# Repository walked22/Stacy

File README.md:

# Stacy

Control PCB for Modified 1995 Geo Tracker 

STACY is a is a custom built printed circuit board that remotely starts, warms up, locks, unlocks and 
tracks a 1995 Geo Tracker. The board was designed with expandability in mind allowing for future upgrades.

Features
- ARM Cortex M0+ microcontroller
- Easy locking connectors to withstand vibrations from offroad driving
- Extra connectors with both analog and digital I/O
- Can recieve commands from RFID and BLE
- Battery monitoring 
- Status RGB LED

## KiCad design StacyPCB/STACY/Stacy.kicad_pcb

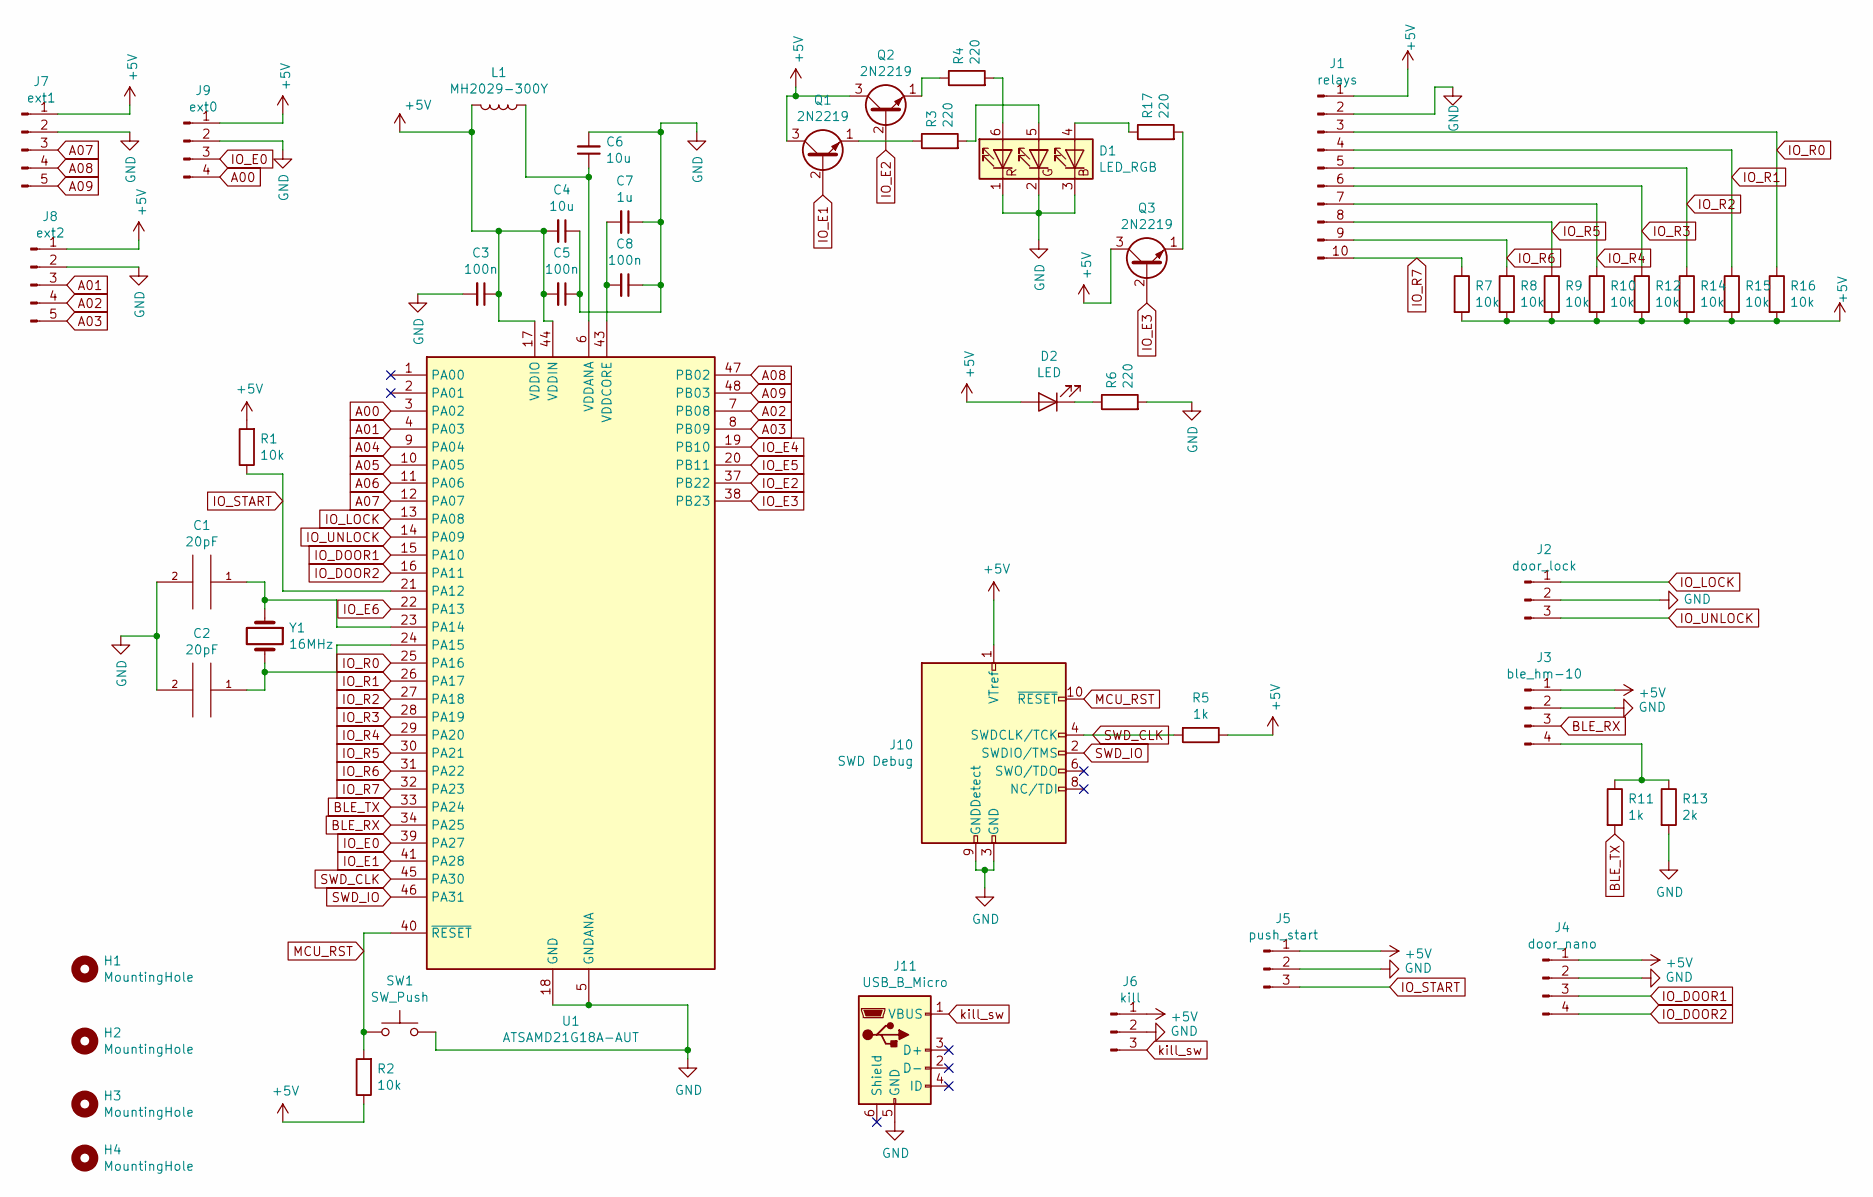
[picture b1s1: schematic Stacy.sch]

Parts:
C1, C2: 20pF; C_0402_1005Metric
C3, C5, C8: 100n; C_0402_1005Metric
C4, C6: 10u; C_0402_1005Metric
C7: 1u; C_0402_1005Metric
D1: LED_RGB; LED_RGB_PLCC-6
D2: LED; LED_0603_1608Metric
H1, H2, H3, H4: MountingHole; MountingHole_2.5mm
J1: relays; JST_EH_B10B-EH-A_1x10_P2.50mm_Vertical
J2: door_lock; JST_EH_B3B-EH-A_1x03_P2.50mm_Vertical
J3: ble_hm-10; JST_EH_B4B-EH-A_1x04_P2.50mm_Vertical
J4: door_nano; JST_EH_B4B-EH-A_1x04_P2.50mm_Vertical
J5: push_start; JST_EH_B3B-EH-A_1x03_P2.50mm_Vertical
J6: kill; JST_EH_B3B-EH-A_1x03_P2.50mm_Vertical
J7: ext1; JST_EH_B5B-EH-A_1x05_P2.50mm_Vertical
J8: ext2; JST_EH_B5B-EH-A_1x05_P2.50mm_Vertical
J9: ext0; JST_EH_B4B-EH-A_1x04_P2.50mm_Vertical
J10: SWD Debug; PinHeader_2x05_P1.27mm_Vertical
J11: USB_B_Micro; USB_Micro-B_Molex_47346-0001
L1: MH2029-300Y; L_0805_2012Metric
Q1, Q2, Q3: 2N2219; TSOT-23
R1, R2, R7, R8, R9, R10, R12, R14, R15, R16: 10k; R_0402_1005Metric
R3, R4, R6, R17: 220; R_0402_1005Metric
R5, R11: 1k; R_0402_1005Metric
R13: 2k; R_0402_1005Metric
SW1: SW_Push; SW_Tactile_Straight_KSA0Axx1LFTR
U1: ATSAMD21G18A-AUT; TQFP-48_7x7mm_P0.5mm
Y1: 16MHz; Crystal_HC49-U_Vertical

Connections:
+5V: C3.1, C4.2, C5.2, D2.2 (A), J1.1, J3.1, J4.1, J5.1, J6.1, J7.1, J8.1, J9.1, J10.1 (VTref), L1.2, Q1.3 (C), Q2.3 (C), Q3.3 (C), R1.2, R2.1, R5.1, R7.2, R8.2, R9.2, R10.2, R12.2, R14.2, R15.2, R16.2, U1.17 (VDDIO), U1.36 (VDDIO), U1.44 (VDDIN)
A00: J9.4, U1.3 (PA02)
A01: J8.3, U1.4 (PA03)
A02: J8.4, U1.7 (PB08)
A03: J8.5, U1.8 (PB09)
A04: U1.9 (PA04)
A05: U1.10 (PA05)
A06: U1.11 (PA06)
A07: J7.3, U1.12 (PA07)
A08: J7.4, U1.47 (PB02)
A09: J7.5, U1.48 (PB03)
BLE_RX: J3.3, U1.34 (PA25)
BLE_TX: R11.2, U1.33 (PA24)
GND: C1.2, C2.2, C3.2, C4.1, C5.1, C6.2, C7.1, C8.1, D1.1 (RK), D1.2 (GK), D1.3 (BK), J1.2, J2.2, J3.2, J4.2, J5.2, J6.2, J7.2, J8.2, J9.2, J10.3 (GND), J10.5 (GND), J10.9 (GNDDetect), J11.5 (GND), R6.2, R13.2, SW1.2, U1.5 (GNDANA), U1.18 (GND), U1.35 (GND), U1.42 (GND)
IO_DOOR1: J4.3, U1.15 (PA10)
IO_DOOR2: J4.4, U1.16 (PA11)
IO_E0: J9.3, U1.39 (PA27)
IO_E1: Q1.2 (B), U1.41 (PA28)
IO_E2: Q2.2 (B), U1.37 (PB22)
IO_E3: Q3.2 (B), U1.38 (PB23)
IO_E4: U1.19 (PB10)
IO_E5: U1.20 (PB11)
IO_E6: U1.22 (PA13)
IO_LOCK: J2.1, U1.13 (PA08)
IO_R0: J1.3, R16.1, U1.25 (PA16)
IO_R1: J1.4, R15.1, U1.26 (PA17)
IO_R2: J1.5, R14.1, U1.27 (PA18)
IO_R3: J1.6, R12.1, U1.28 (PA19)
IO_R4: J1.7, R10.1, U1.29 (PA20)
IO_R5: J1.8, R9.1, U1.30 (PA21)
IO_R6: J1.9, R8.1, U1.31 (PA22)
IO_R7: J1.10, R7.1, U1.32 (PA23)
IO_START: J5.3, R1.1, U1.21 (PA12)
IO_UNLOCK: J2.3, U1.14 (PA09)
MCU_RST: J10.10 (~RESET~), R2.2, SW1.1, U1.40 (~RESET)
unnamed: C1.1, U1.23 (PA14), Y1.1
unnamed: C2.1, U1.24 (PA15), Y1.2
unnamed: C6.1, L1.1, U1.6 (VDDANA)
unnamed: C7.2, C8.2, U1.43 (VDDCORE)
unnamed: D1.4 (BA), R17.1
unnamed: D1.5 (GA), R3.2
unnamed: D1.6 (RA), R4.2
unnamed: D2.1 (K), R6.1
unnamed: J3.4, R11.1, R13.1
unnamed: Q1.1 (E), R3.1
unnamed: Q2.1 (E), R4.1
unnamed: Q3.1 (E), R17.2
SWD_CLK: J10.4 (SWDCLK/TCK), R5.2, U1.45 (PA30)
SWD_IO: J10.2 (SWDIO/TMS), U1.46 (PA31)
kill_sw: J6.3, J11.1 (VBUS)

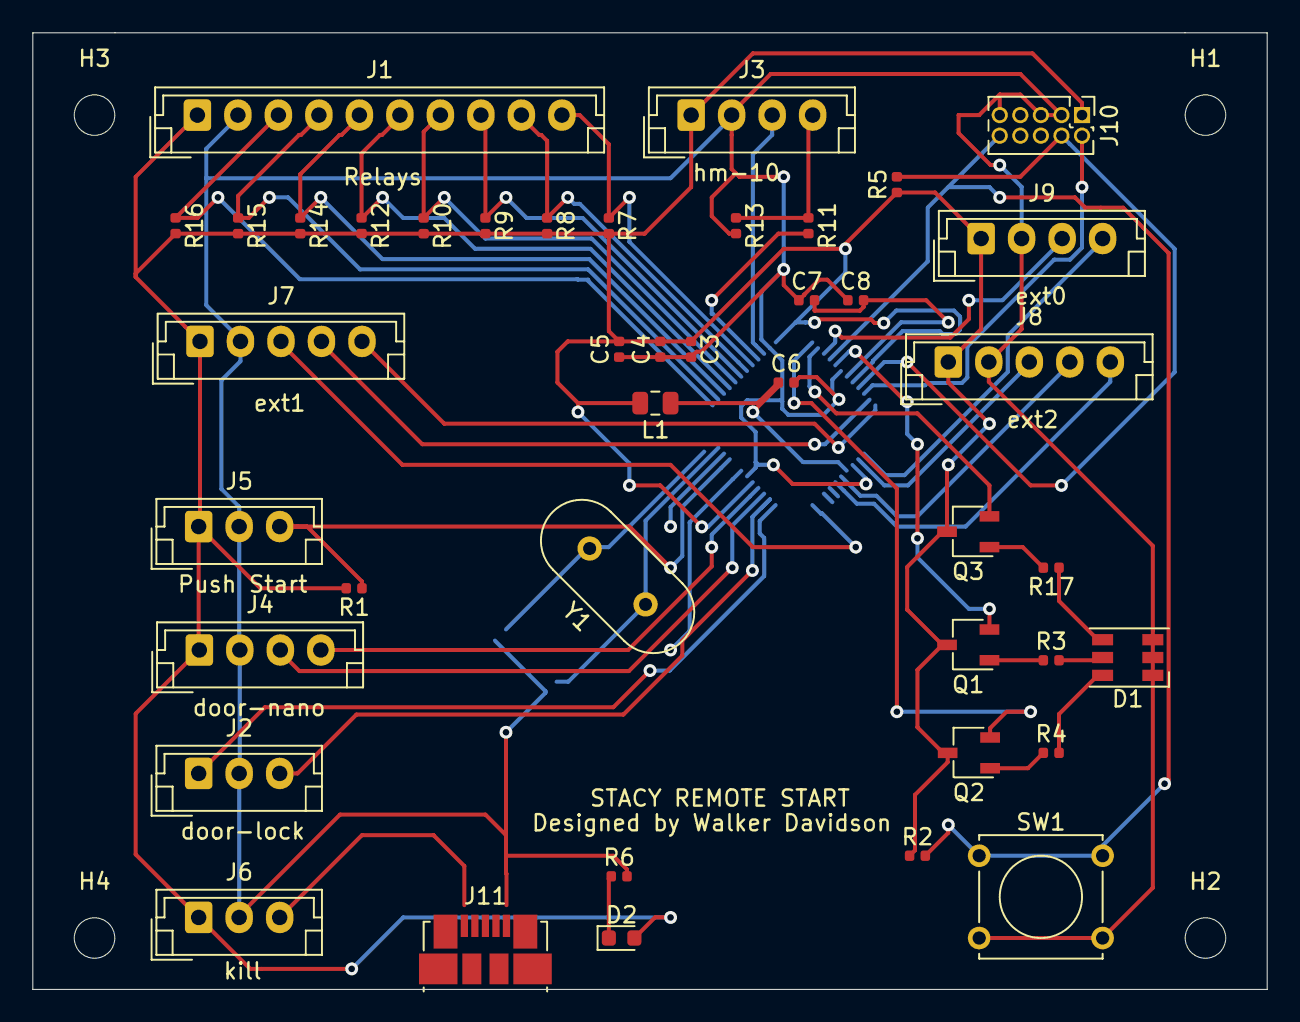
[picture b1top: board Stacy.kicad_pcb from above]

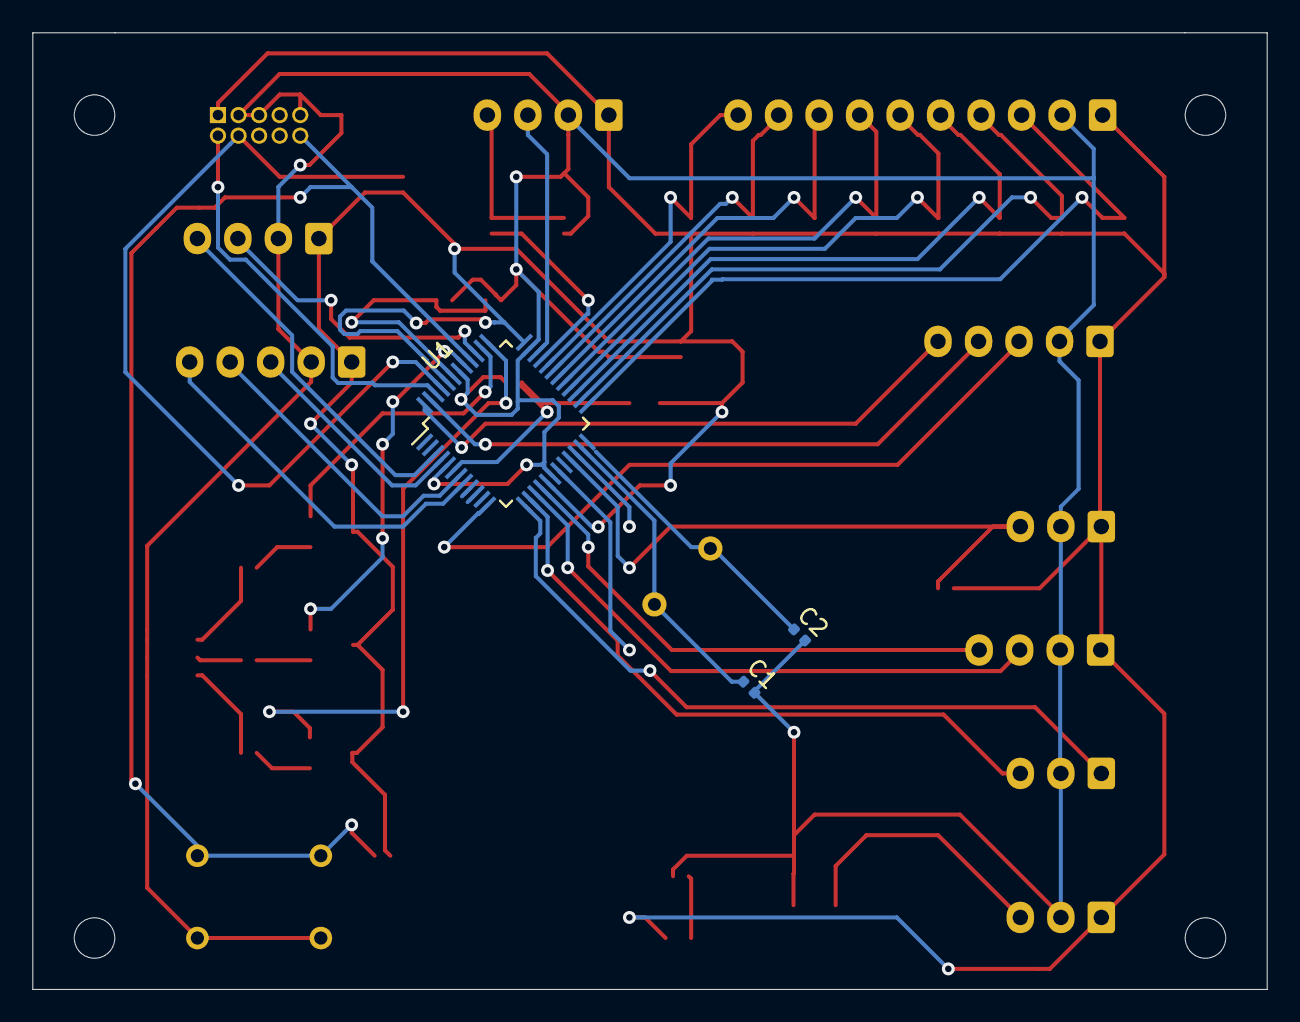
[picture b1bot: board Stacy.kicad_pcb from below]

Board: 2 copper layers, 76.2 x 59.1 mm, 49 parts (3 on the bottom side), 44 nets.

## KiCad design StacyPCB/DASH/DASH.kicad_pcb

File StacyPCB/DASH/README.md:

# Stacy

Voltage Divider PCB for Modified 1995 Geo Tracker Dash Board 

Built to take 12V input and divide down to 3.3V ideal for Raspberry Pi GPIO signals
Features
- 11 12V inputs with ground via locking JST connector
- 11 3.3V outputs with locking JST connector

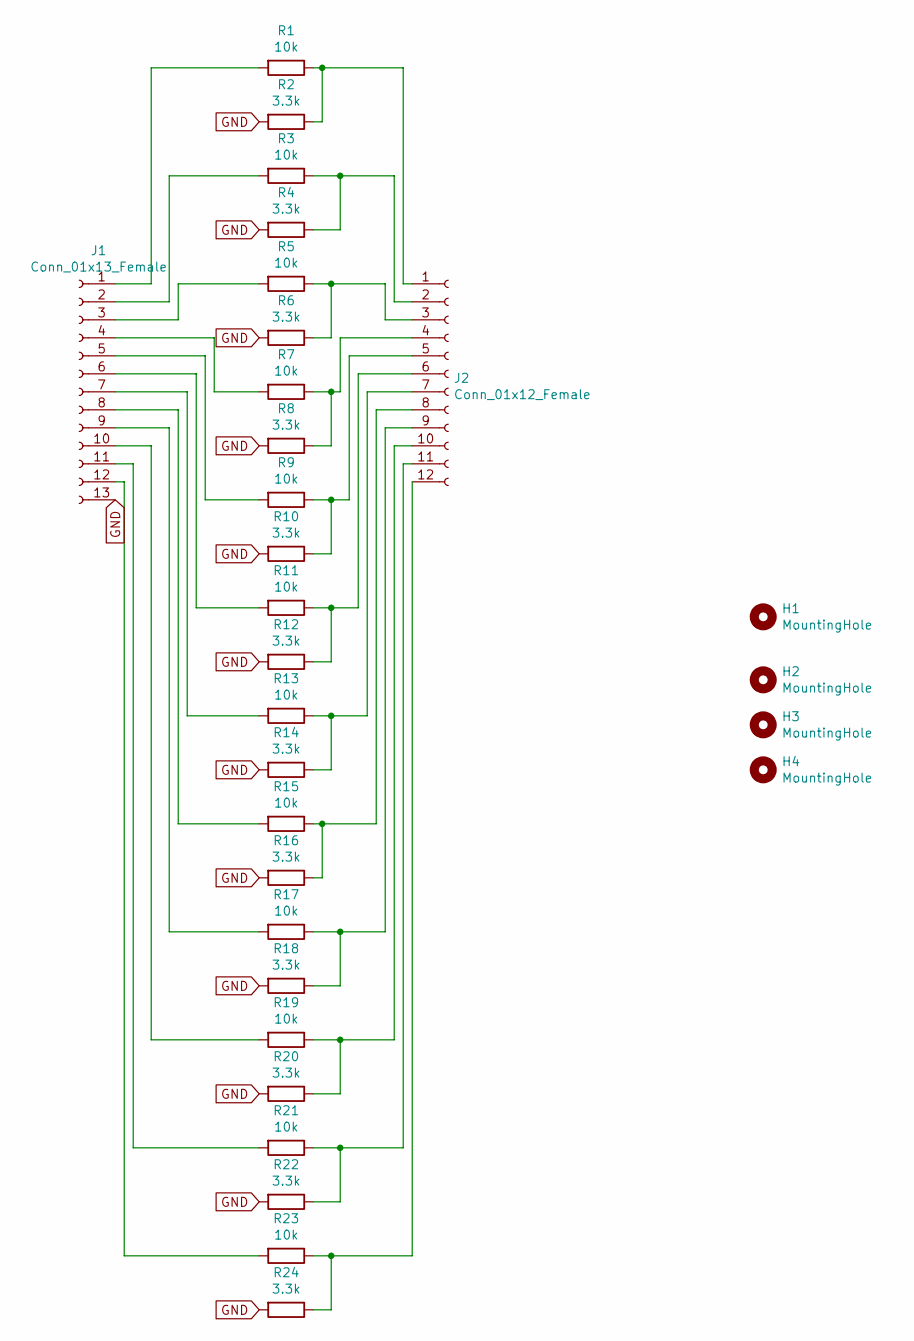
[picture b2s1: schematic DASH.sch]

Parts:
H1, H2, H3, H4: MountingHole; MountingHole_2.2mm_M2
J1: Conn_01x13_Female; JST_EH_S13B-EH_1x13_P2.50mm_Horizontal
J2: Conn_01x12_Female; JST_EH_S12B-EH_1x12_P2.50mm_Horizontal
R1, R3, R5, R7, R9, R11, R13, R15, R17, R19, R21, R23: 10k; R_Axial_DIN0207_L6.3mm_D2.5mm_P10.16mm_Horizontal
R2, R4, R6, R8, R10, R12, R14, R16, R18, R20, R22, R24: 3.3k; R_Axial_DIN0207_L6.3mm_D2.5mm_P10.16mm_Horizontal

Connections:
GND: J1.13, R2.2, R4.2, R6.2, R8.2, R10.2, R12.2, R14.2, R16.2, R18.2, R20.2, R22.2, R24.2
unnamed: J1.1, R1.2
unnamed: J1.2, R3.2
unnamed: J1.3, R5.2
unnamed: J1.4, R7.2
unnamed: J1.5, R9.2
unnamed: J1.6, R11.2
unnamed: J1.7, R13.2
unnamed: J1.8, R15.2
unnamed: J1.9, R17.2
unnamed: J1.10, R19.2
unnamed: J1.11, R21.2
unnamed: J1.12, R23.2
unnamed: J2.1, R1.1, R2.1
unnamed: J2.2, R3.1, R4.1
unnamed: J2.3, R5.1, R6.1
unnamed: J2.4, R7.1, R8.1
unnamed: J2.5, R9.1, R10.1
unnamed: J2.6, R11.1, R12.1
unnamed: J2.7, R13.1, R14.1
unnamed: J2.8, R15.1, R16.1
unnamed: J2.9, R17.1, R18.1
unnamed: J2.10, R19.1, R20.1
unnamed: J2.11, R21.1, R22.1
unnamed: J2.12, R23.1, R24.1

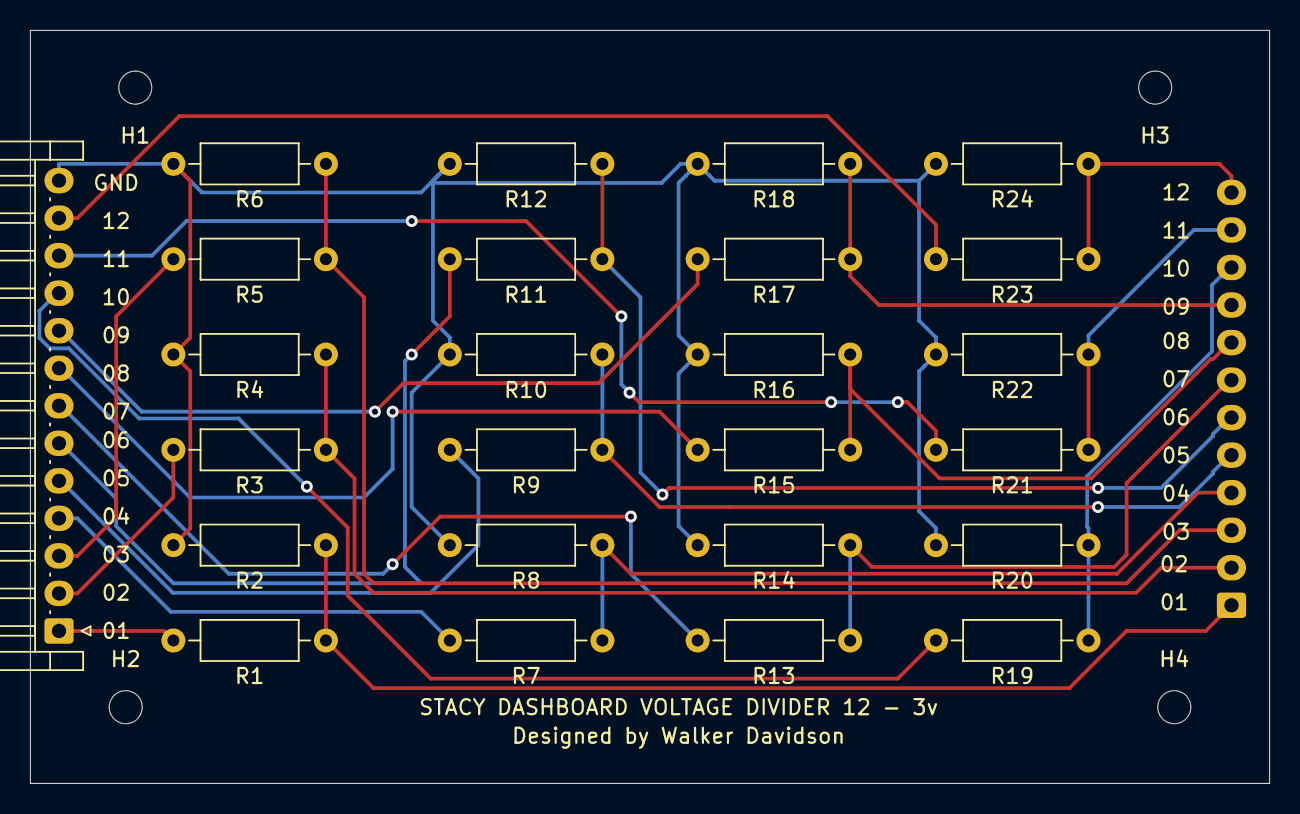
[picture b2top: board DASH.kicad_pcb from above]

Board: 2 copper layers, 82.6 x 50.2 mm, 30 parts (1 on the bottom side), 25 nets.

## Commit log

2019-11-26 created git repo for Stacy
2019-11-26 created git repo for stacy pcb
2019-11-26 Added git repo for remote starting
2019-11-26 Changed color of up and down buttons
2019-11-26 AC button now chenges color when checked
2019-11-26 Changed spaces to tabs
2019-11-27 Fixed AC color
2019-11-27 Fixed AC color(again)
2019-11-27 Fixed AC startup color
2019-11-27 Fixed circ color
2019-11-27 changed color to variable
2019-11-27 fixed color variable name
2019-11-27 Send values on startup
2019-11-27 Increased delay time between serial comm
2019-11-27 Added temp startup
2019-11-28 Added git repo for dashboard voltage divider
2019-11-29 Routed all decoupling caps and fixed clock footprint. This version has been manufactured
2019-11-29 Create Images
2019-11-29 Added images of STACY PCB
2019-11-29 Changed background color of top view
2019-11-29 Fixed color
2019-12-12 Created .gitignore
2019-12-12 Removed drl and gbr files
2019-12-12 removed backups
2019-12-12 Moved readme to correct location
2019-12-12 Added images of voltage divider board
2019-12-12 Created Readme
2019-12-20 added internal temperature display
2019-12-20 removed self from emit
2019-12-20 moved while loop
2019-12-20 added self to thread functions
2019-12-20 added self to functions
2019-12-20 added self
2019-12-20 removed while loop
2019-12-20 added emit
2019-12-20 fixed spelling error
2019-12-20 added while loop
2019-12-20 added _del_ function
2019-12-20 Added thread starter
2019-12-20 Added colon to while loop
2019-12-20 fixed threading(first working)
2019-12-20 Added nice labels for temp
2019-12-20 Fixed name of label
2019-12-20 changed color of labels
2019-12-20 limited number of decimal points
2019-12-21 added code for second temp sensor
2019-12-21 moved labels
2019-12-21 added function for hot or cold start
2019-12-21 added int
2019-12-21 made hot or cold start into function
2019-12-21 changed int to float
2019-12-21 changed num to global
2019-12-21 changed count to global
2019-12-21 set dial when starting hot
2019-12-21 Created folder for instrument cluster
2019-12-21 Adjusted window size
2019-12-22 Added rotating geo picture
2019-12-22 Added functional RPM gauge
2019-12-24 Created data sending simulator
2019-12-24 Added back view of car and angle readouts
2019-12-24 added Temp and fuel gauges
2019-12-25 Added warning light indicators and corresponding images
2019-12-25 Added image for readme
2020-01-16 created startup animation and audio
2020-01-28 fixed transistor
2020-04-03 Created collector script
2020-04-03 fixed print line
2020-04-03 First attempt at measuring RPM
2022-12-18 Creating new ui folder
2022-12-18 added breeze theme
2023-05-07 initial commit for 2023 updates
2023-05-08 added graphics view for rotating pixmaps
2023-10-23 Updated filepaths
2023-10-23 updated photos
2023-10-23 expand slider size
2023-10-24 upsized slider handles
2023-11-05 added serial write
2023-11-05 housekeeping?
2023-11-05 fixed sliders
2023-11-06 installed updates
2023-11-06 test script for accelerometer
2023-11-06 rotating pitch/yaw
2023-11-06 fixed label names
2023-11-07 fixed pitch/yaw labels
2024-02-20 added relay controls
2024-03-13 changed to sliders for pitch and roll, added temp sensors
2024-03-14 updated images for inside and outside temp display, added startup scripts
2025-07-04 new climate control files
2025-07-05 made it all work kinda
2025-07-05 made more better
2025-07-08 fixed stuff kinda
